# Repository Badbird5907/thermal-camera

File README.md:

# Thermal Camera
[Video Demo](https://www.youtube.com/shorts/hk5CXilCE_w)

**This project was posted to [Hackaday](https://hackaday.com/2025/08/10/cheap-thermal-camera-fits-the-bill/)!**

This is my design of a cheap and affordable thermal camera (< $60, excl shipping)!. It utilizes the MLX90640 as the image sensor, and the esp32 to process and display the images on a TFT LCD screen.

I made this project because off the shelf thermal cameras are exuberantly expensive, and I need one to figure out if my PCBs are shorting.

The hardest part of this project so far was designing the battery charging circuit, as I needed to use multiple ICs to charge the battery, keep the voltage stable, and to keep the battery from overcharging.

# Screenshots

-> The case (and PCB) isn't very well designed, If I redesigned this project, i'd make the pcb smaller and integrate the LCD...

# Photos

# Firmware
You can find the firmware in the `thermal_camera` folder.

The firmware is written with the Arduino IDE. The ESP32 is used to read the thermal camera and display the images on the TFT LCD screen.

## Firmware Setup
1. Open the Arduino IDE.
2. Install the TFT_eSPI library and MLX90640 library by Adafruit.
3. Create a thermal_camera.h file in `C:\Users\YourUsername\Documents\Arduino\libraries\TFT_eSPI\User_Setups`
4. Paste in the following code:
```c
#define ILI9341_DRIVER
#define TFT_WIDTH 240 
#define TFT_HEIGHT 320 

#define TFT_MISO 8 
#define TFT_MOSI 6 
#define TFT_SCLK 5 
#define TFT_CS 15 
#define TFT_DC 4 
#define TFT_RST 16 
#define TFT_BL 7 

#define TOUCH_CS 10

#define SPI_FREQUENCY 40000000
```
5. Open `C:\Users\YourUsername\Documents\Arduino\libraries\TFT_eSPI\User_Setup_Select.h`
6. Add the line `#include <User_Setups/thermal_camera.h>` to the file under User_Setup.h
7. Compile and upload the firmware to the ESP32.

# BOM
The total cost of the project is about $86 USD: ([Spreadsheet](https://docs.google.com/spreadsheets/d/1PjPY5GV_mC4sFPF-p1Rz1wbnOWLJnwNhDzCwLhk1jFM/edit?usp=sharing))

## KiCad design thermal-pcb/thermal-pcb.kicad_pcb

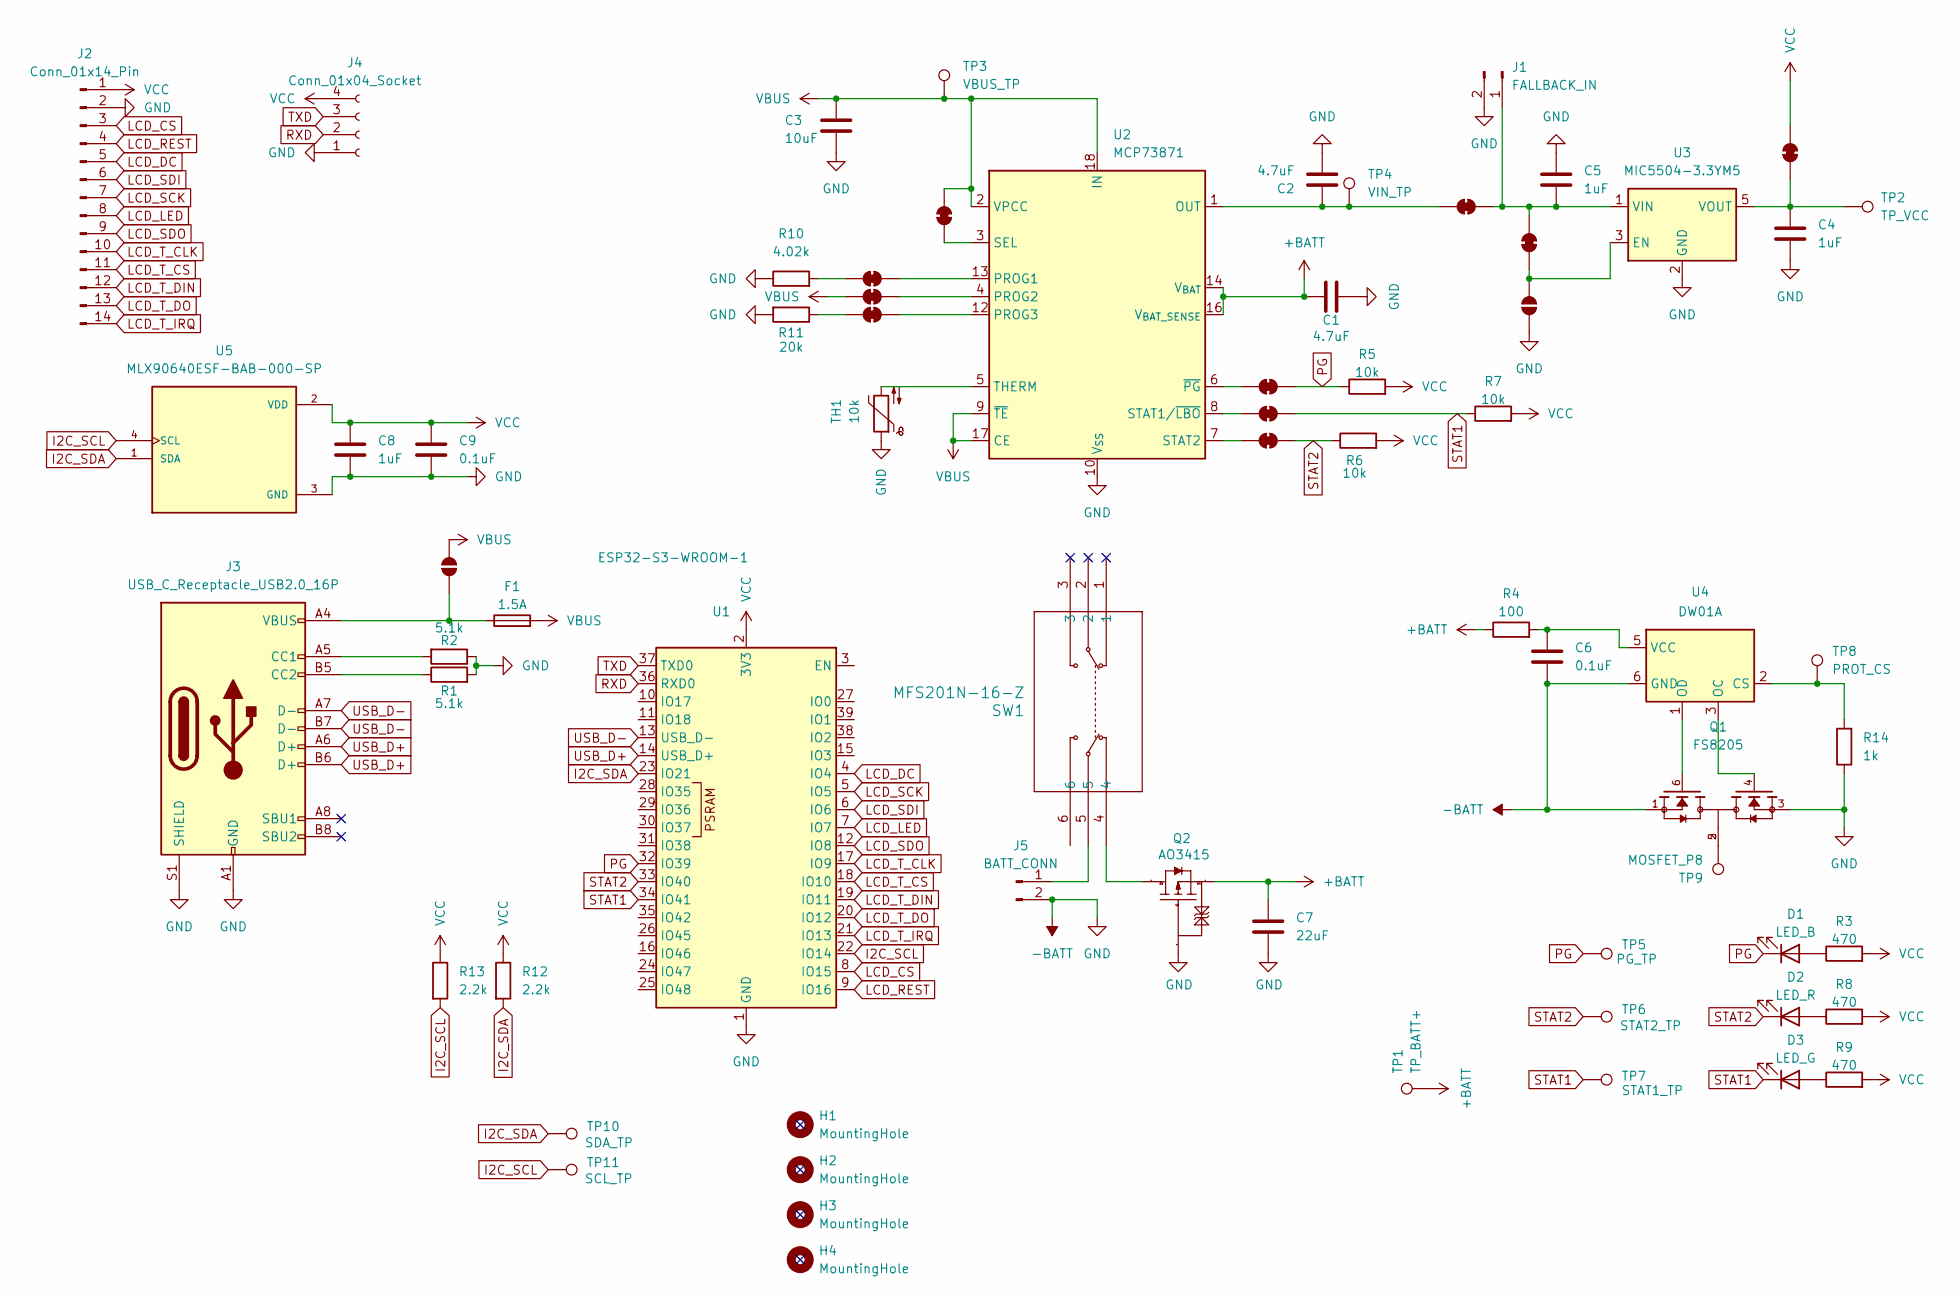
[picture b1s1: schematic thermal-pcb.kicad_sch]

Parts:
C1, C2: 4.7uF; C_0805_2012Metric
C3: 10uF; C_0805_2012Metric
C4, C5, C8: 1uF; C_0805_2012Metric
C6, C9: 0.1uF; C_0805_2012Metric
C7: 22uF; C_0805_2012Metric
D1: LED_B; LED_1206_3216Metric
D2: LED_R; LED_1206_3216Metric
D3: LED_G; LED_1206_3216Metric
F1: 1.5A; Fuse_1206_3216Metric
H1, H2, H3, H4: MountingHole; MountingHole_4.3mm_M4
J1: FALLBACK_IN; PinHeader_1x02_P2.54mm_Vertical
J2: Conn_01x14_Pin; PinSocket_1x14_P2.54mm_Vertical
J3: USB_C_Receptacle_USB2.0_16P; USB_C_Receptacle_GCT_USB4105-xx-A_16P_TopMnt_Horizontal
J4: Conn_01x04_Socket; PinSocket_1x04_P2.54mm_Vertical
J5: BATT_CONN; PinSocket_1x02_P2.54mm_Vertical
JP1: EN_VCC; SolderJumper-2_P1.3mm_Bridged_RoundedPad1.0x1.5mm
JP2: EN_GND; SolderJumper-2_P1.3mm_Open_RoundedPad1.0x1.5mm
JP3: PROG1_JP; SolderJumper-2_P1.3mm_Bridged_RoundedPad1.0x1.5mm
JP4: PROG2_JP; SolderJumper-2_P1.3mm_Bridged_RoundedPad1.0x1.5mm
JP5: PROG3_JP; SolderJumper-2_P1.3mm_Bridged_RoundedPad1.0x1.5mm
JP6: SEL_JP; SolderJumper-2_P1.3mm_Bridged_RoundedPad1.0x1.5mm
JP7: PG_JP; SolderJumper-2_P1.3mm_Bridged_RoundedPad1.0x1.5mm
JP8: STAT1_JP; SolderJumper-2_P1.3mm_Bridged_RoundedPad1.0x1.5mm
JP9: STAT2_JP; SolderJumper-2_P1.3mm_Bridged_RoundedPad1.0x1.5mm
JP10: VCC_JP; SolderJumper-2_P1.3mm_Bridged_RoundedPad1.0x1.5mm
JP11: BMS_VOUT; SolderJumper-2_P1.3mm_Bridged_RoundedPad1.0x1.5mm
JP12: FUSE_BYPASS; SolderJumper-2_P1.3mm_Open_RoundedPad1.0x1.5mm
Q1: FS8205; SOT95P280X145-6N; PARTREV 1.9
Q2: AO3415; SOT-23-3_L2.9-W1.3-P1.90-LS2.4-BR; Manufacturer Part AO3415; LCSC Part Name 1个P沟道 耐压:20V 电流:4A
R1, R2: 5.1k; R_0805_2012Metric
R3, R8, R9: 470; R_0805_2012Metric
R4: 100; R_0805_2012Metric
R5, R6, R7: 10k; R_0805_2012Metric
R10: 4.02k; R_0805_2012Metric
R11: 20k; R_0805_2012Metric
R12, R13: 2.2k; R_0805_2012Metric
R14: 1k; R_0805_2012Metric
SW1: MFS201N-16-Z; MFS201N-16-Z_NDC
TH1: 10k; R_0805_2012Metric
TP1: TP_BATT+; TestPoint_Pad_D1.5mm
TP2: TP_VCC; TestPoint_Pad_D1.5mm
TP3: VBUS_TP; TestPoint_Pad_D1.5mm
TP4: VIN_TP; TestPoint_Pad_D1.5mm
TP5: PG_TP; TestPoint_Pad_D1.5mm
TP6: STAT2_TP; TestPoint_Pad_D1.5mm
TP7: STAT1_TP; TestPoint_Pad_D1.5mm
TP8: PROT_CS; TestPoint_Pad_D1.5mm
TP9: MOSFET_P8; TestPoint_Pad_D1.5mm
TP10: SDA_TP; TestPoint_Pad_D1.5mm
TP11: SCL_TP; TestPoint_Pad_D1.5mm
U1: ESP32-S3-WROOM-1
U2: MCP73871; QFN-20-1EP_4x4mm_P0.5mm_EP2.5x2.5mm
U3: MIC5504-3.3YM5; SOT-23-5
U4: DW01A; SOT-23-6
U5: MLX90640ESF-BAB-000-SP; TO292P945H1165-4; PARTREV 11

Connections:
+BATT: C1.1, C7.1, Q2.2 (S), R4.1, TP1.1, U2.14 (V_{BAT}), U2.15 (V_{BAT}), U2.16 (V_{BAT_SENSE})
-BATT: C1.2, C2.2, C3.2, C4.2, C5.1, C6.2, C7.2, C8.2, C9.2, J1.2, J2.2, J3.A1 (GND), J3.A12 (GND), J3.B1 (GND), J3.B12 (GND), J3.S1 (SHIELD), J4.1, J5.2, JP2.1 (A), Q1.1, Q1.3, Q2.1 (G), R1.2, R2.1, R10.1, R11.2, R14.1, TH1.1, U1.1 (GND), U1.40 (GND), U1.41 (GND), U2.10 (V_{SS}), U2.11 (V_{SS}), U2.21 (V_{SS}), U3.2 (GND), U4.6 (GND), U5.3 (GND)
I2C_SCL: R13.2, TP11.1, U1.22 (IO14), U5.4 (SCL)
I2C_SDA: R12.2, TP10.1, U1.23 (IO21), U5.1 (SDA)
LCD_CS: J2.3, U1.8 (IO15)
LCD_DC: J2.5, U1.4 (IO4)
LCD_LED: J2.8, U1.7 (IO7)
LCD_REST: J2.4, U1.9 (IO16)
LCD_SCK: J2.7, U1.5 (IO5)
LCD_SDI: J2.6, U1.6 (IO6)
LCD_SDO: J2.9, U1.12 (IO8)
LCD_T_CLK: J2.10, U1.17 (IO9)
LCD_T_CS: J2.11, U1.18 (IO10)
LCD_T_DIN: J2.12, U1.19 (IO11)
LCD_T_DO: J2.13, U1.20 (IO12)
LCD_T_IRQ: J2.14, U1.21 (IO13)
unnamed: D1.2 (A), R3.1
unnamed: D2.2 (A), R8.1
unnamed: D3.2 (A), R9.1
unnamed: C5.2, J1.1, JP1.1 (A), JP11.1 (A), U3.1 (VIN)
unnamed: J3.A5 (CC1), R2.2
unnamed: J3.B5 (CC2), R1.1
unnamed: J5.1, SW1.5
unnamed: JP1.2 (B), JP2.2 (B), U3.3 (EN)
unnamed: JP3.1 (A), R10.2
unnamed: JP3.2 (B), U2.13 (PROG1)
unnamed: JP4.1 (A), U2.4 (PROG2)
unnamed: JP5.1 (A), U2.12 (PROG3)
unnamed: JP5.2 (B), R11.1
unnamed: JP6.1 (A), U2.3 (SEL)
unnamed: JP7.1 (A), U2.6 (~PG)
unnamed: JP8.1 (A), U2.8 (STAT1/~LBO)
unnamed: JP9.1 (A), U2.7 (STAT2)
unnamed: C4.1, JP10.2 (B), TP2.1, U3.5 (VOUT)
unnamed: C2.1, JP11.2 (B), TP4.1, U2.1 (OUT), U2.20 (OUT)
unnamed: F1.1, J3.A4 (VBUS), J3.A9 (VBUS), J3.B4 (VBUS), J3.B9 (VBUS), JP12.1 (A)
unnamed: Q1.2, Q1.5, TP9.1
unnamed: Q2.3 (D), SW1.4
unnamed: TH1.2, U2.5 (THERM)
unnamed: R14.2, TP8.1, U4.2 (CS)
unnamed: Q1.4, U4.3 (OC)
unnamed: Q1.6, U4.1 (OD)
unnamed: C6.1, R4.2, U4.5 (VCC)
PG: D1.1 (K), JP7.2 (B), R5.1, TP5.1, U1.32 (IO39)
RXD: J4.2, U1.36 (RXD0)
STAT1: D3.1 (K), JP8.2 (B), R7.1, TP7.1, U1.34 (IO41)
STAT2: D2.1 (K), JP9.2 (B), R6.1, TP6.1, U1.33 (IO40)
TXD: J4.3, U1.37 (TXD0)
USB_D+: J3.A6 (D+), J3.B6 (D+), U1.14 (USB_D+)
USB_D-: J3.A7 (D-), J3.B7 (D-), U1.13 (USB_D-)
VBUS: C3.1, F1.2, JP4.2 (B), JP6.2 (B), JP12.2 (B), TP3.1, U2.2 (VPCC), U2.9 (~TE), U2.17 (CE), U2.18 (IN), U2.19 (IN)
VCC: C8.1, C9.1, J2.1, J4.4, JP10.1 (A), R3.2, R5.2, R6.2, R7.2, R8.2, R9.2, R12.1, R13.1, U1.2 (3V3), U5.2 (VDD)

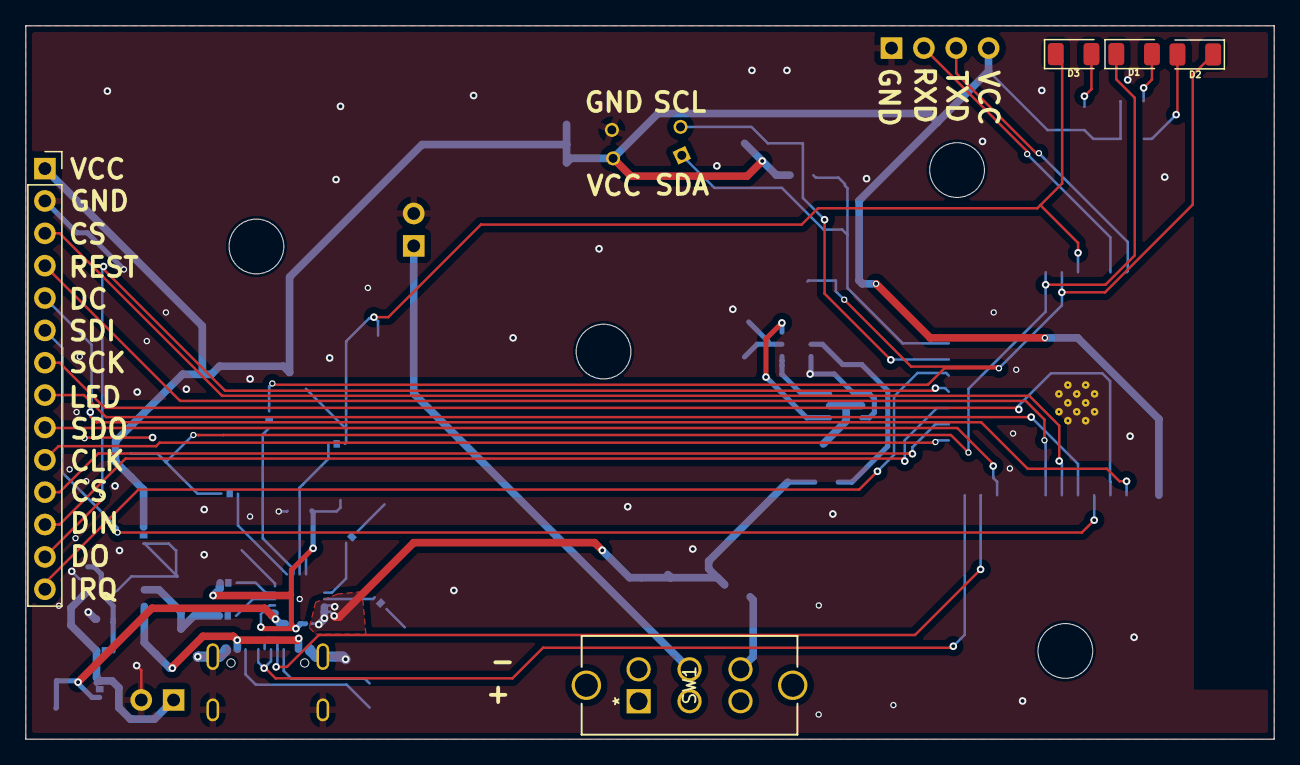
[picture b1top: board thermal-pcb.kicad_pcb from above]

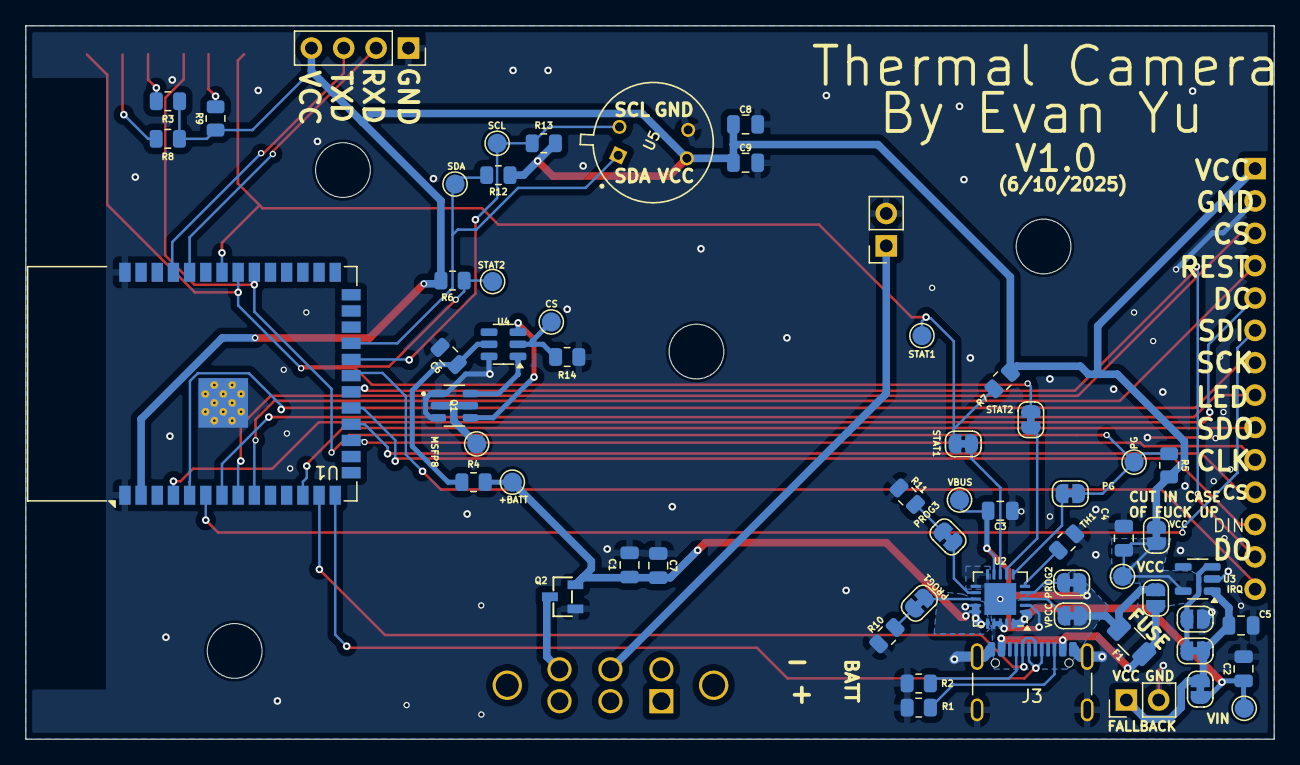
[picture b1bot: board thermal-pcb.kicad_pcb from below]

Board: 2 copper layers, 98.0 x 56.0 mm, 68 parts (59 on the bottom side), 52 nets.

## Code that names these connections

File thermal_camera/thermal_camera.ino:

#include <Wire.h>
#include <Adafruit_MLX90640.h>
#include <SPI.h>
#include <TFT_eSPI.h>

#define LCD_LED_PIN 7
#define I2C_SCL_PIN 14
#define I2C_SDA_PIN 21

Adafruit_MLX90640 mlx;
float frame[32 * 24]; // 32x24 pixels

TFT_eSPI tft = TFT_eSPI(); // init display

uint16_t colormap[256]; // color palette temp -> color

bool autoScale = true;
float fixedMin = 20.0;
float fixedMax = 35.0;

void setup() {
  Serial.begin(9600);

  // init I2C
  Wire.begin(I2C_SDA_PIN, I2C_SCL_PIN);
  Wire.setClock(400000); // 400kHz

  // init thermal camera
  if (!mlx.begin(MLX90640_I2CADDR_DEFAULT, &Wire)) {
    Serial.println("No MLX90640 found!");
    while (1) delay(10);
  }

  mlx.setRefreshRate(MLX90640_4_HZ);

  // init TFT display
  tft.init();
  tft.setRotation(2); // Rotate 180 degrees to fix upside-down image
  tft.fillScreen(TFT_BLACK);

  // set backlight
  pinMode(LCD_LED_PIN, OUTPUT);
  digitalWrite(LCD_LED_PIN, HIGH);

  generateColormap();
}

void loop() {
  if (mlx.getFrame(frame) != 0) { // read frame
    Serial.println("No frame data");
    delay(500);
    return;
  }

  // find min and max temperatures for auto-scaling
  float minTemp = 100;
  float maxTemp = 0;

  if (autoScale) {
    for (int i = 0; i < 32 * 24; i++) {
      if (frame[i] > 0 && frame[i] < 100) { // filter invalid readings
        minTemp = min(minTemp, frame[i]);
        maxTemp = max(maxTemp, frame[i]);
      }
    }

    // prevent too narrow temperature range
    if (maxTemp - minTemp < 5.0) {
      float midTemp = (maxTemp + minTemp) / 2;
      minTemp = midTemp - 2.5;
      maxTemp = midTemp + 2.5;
    }
  } else {
    // use fixed range
    minTemp = fixedMin;
    maxTemp = fixedMax;
  }

  displayThermalImage(minTemp, maxTemp);

  tft.setTextColor(TFT_WHITE, TFT_BLACK); // show min and max temperatures
  tft.setTextSize(2);
  tft.setCursor(10, 10);
  tft.print("Min: ");
  tft.print(minTemp, 1);
  tft.print("C");

  tft.setCursor(10, 40);
  tft.print("Max: ");
  tft.print(maxTemp, 1);
  tft.print("C");

  delay(250);
}

void generateColormap() { // generate color palette
  for (int i = 0; i < 256; i++) {
    if (i < 64) {
      colormap[i] = tft.color565(0, 0, i * 4); // black to blue
    } else if (i < 128) {
      colormap[i] = tft.color565(0, (i - 64) * 4, 255); // blue to cyan
    } else if (i < 192) {
      colormap[i] = tft.color565((i - 128) * 4, 255, 255 - (i - 128) * 4); // cyan to yellow
    } else {
      colormap[i] = tft.color565(255, 255 - (i - 192) * 4, 0); // yellow to red
    }
  }
}

void displayThermalImage(float minTemp, float maxTemp) { // display thermal image on TFT
  // calculate display size and scaling
  int displayWidth = tft.width();
  int displayHeight = tft.height();

  // scale pixel to display size
  int pixelWidth = displayWidth / 32;
  int pixelHeight = (displayHeight - 100) / 24; // reserve space for text

  // center image
  int offsetX = (displayWidth - (32 * pixelWidth)) / 2;
  int offsetY = 70; // space at top for text

  // display each thermal pixel
  for (int y = 0; y < 24; y++) {
    for (int x = 0; x < 32; x++) {
      // Flip horizontally by reversing the x-coordinate
      int flippedX = 31 - x; // Flip the x-coordinate (32 pixels wide)

      float temp = frame[y * 32 + flippedX];

      // map temp to color index
      int colorIndex;
      if (temp < minTemp) colorIndex = 0;
      else if (temp > maxTemp) colorIndex = 255;
      else colorIndex = map(temp * 100, minTemp * 100, maxTemp * 100, 0, 255);

      tft.fillRect( // one pixel
        offsetX + x * pixelWidth, // Use the original x-coordinate for display
        offsetY + y * pixelHeight,
        pixelWidth,
        pixelHeight,
        colormap[colorIndex]
      );
    }
  }

  // scale bar
  int barHeight = 20;
  int barWidth = displayWidth - 40;
  int barX = 20;
  int barY = displayHeight - 30;

  for (int i = 0; i < barWidth; i++) {
    int colorIndex = map(i, 0, barWidth - 1, 0, 255);
    tft.drawFastVLine(barX + i, barY, barHeight, colormap[colorIndex]);
  }

  // color scale label
  tft.setTextColor(TFT_WHITE, TFT_BLACK);
  tft.setTextSize(1);
  tft.setCursor(barX, barY - 15);
  tft.print(minTemp, 1);
  tft.print("C");

  tft.setCursor(barX + barWidth - 40, barY - 15);
  tft.print(maxTemp, 1);
  tft.print("C");
}

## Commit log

2025-05-29 kicad
2025-05-29 work on pcb
2025-05-30 stuff
2025-05-30 work on schematic
2025-06-01 schematic
2025-06-01 remove backups
2025-06-01 5/31
2025-06-01 work
2025-06-01 temp
2025-06-01 route most traces
2025-06-03 some stuff
2025-06-03 journal
2025-06-03 remove lock
2025-06-05 almost done pcb
2025-06-05 finish pcb
2025-06-05 Case
2025-06-05 remove lock file
2025-06-09 add firmware
2025-06-14 update pcb + bom to use aliexpress stuff
2025-06-14 update time
2025-06-14 use cheaper shipping for jlc
2025-06-14 expand journal
2025-06-14 forgot some things
2025-07-26 fix: image orientation
2025-08-13 update case + readme
2025-08-13 add MIT license (closes #1)
